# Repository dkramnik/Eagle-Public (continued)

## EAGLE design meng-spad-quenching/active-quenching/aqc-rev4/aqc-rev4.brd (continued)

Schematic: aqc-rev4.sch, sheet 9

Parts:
C26: CAP ALUM POLY 47UF 20% 20V SMD; CT7343
C79, C106, C107: CAP CER 0.1UF 25V X7R 0603 10%; C0603
C95: CAP CER 0.1UF 10V X7R 0402 10%; C0402
C97: CAP CER 10000PF 10V X7R 0402 10%; C0402
C98, C101: CAP CER 47PF 16V C0G 0402 5%; C0402
C105: CAP CER 10000PF 25V X7R 0603 10%; C0603
C108: CAP CER 4.7UF 6.3V X7R 0603 10%; C0603
H1, H2, H3, H4: MOUNT-PAD-ROUND3.2; 3,2-PAD
IC29: USBLC6-2SC6Y; SOT23-6L
IC32: LM1117; SOT-223
L8, L10: MI0805J102R-10; R0805
Q1: DMG2305UX-13; SOT23-WIDE
R58: RES SMD 4.7K OHM 1% 1/10W 0603; R0603
R62: RES SMD 100K OHM 1% 1/10W 0603; R0603
R67, R70: RES SMD 22 OHM 1% 1/10W 0402; R0402
TP23: TPTP15R; TP15R
X3, X6: KEYSTONE-7774
X8: 61729-0010BLF; PN61729-S

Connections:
!MCU_SMPS_PRECHG: R58.2; also elsewhere on the board
GND: C26.-, C95.2, C97.2, C98.2, C101.2, C105.2, C106.2, C107.2, C108.2, H1.B3,2, H2.B3,2, H3.B3,2, H4.B3,2, IC29.2 (GND), IC32.1 (GND), L10.2, X3.1, X3.2, X3.3, X3.4, X6.1, X6.2, X6.3, X6.4, X8.S1, X8.S2; also elsewhere on the board
MCU_USB_FS_D_N: C101.1, R70.1; also elsewhere on the board
MCU_USB_FS_D_P: C98.1, R67.1; also elsewhere on the board
unnamed: C79.1, Q1.1 (G), R58.1, R62.1
PP_P3V3: C95.1, C97.1, C106.1, IC29.5 (VBUS), IC32.2 (OUT), IC32.4 (TAB), TP23.TP; also elsewhere on the board
SMPS_USB_VDD: C26.+, C79.2, Q1.3 (D); also elsewhere on the board
USBCONN_P1: C105.1, L8.1, X8.1
USBCONN_P4: L10.1, X8.4
USBD_CONN_N: IC29.3 (I/O2), X8.2
USBD_CONN_P: IC29.1 (I/O1_1), X8.3
USBD_TVS_N: IC29.4 (I/O2_2), R70.2
USBD_TVS_P: IC29.6 (I/O1_2), R67.2
USB_VDD: C107.1, C108.1, IC32.3 (IN), L8.2, Q1.2 (S), R62.2

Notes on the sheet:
USB INPUT AND INRUSH LIMITING
3.0
1 of 1

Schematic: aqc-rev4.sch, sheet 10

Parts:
C3: CAP CER 1000PF 50V X7R 0603 10%; C0603
C4: CAP CER 1300PF 50V C0G 0603 5%; C0603
C13, C14, C25: CAP ALUM POLY 47UF 20% 20V SMD; CT7343
C15: CAP CER 4.7UF 25V X7R 0805 10%; C0805
C17: CAP CER 0.1UF 25V X7R 0603 10%; C0603
C18: CAP CER 0.015UF 50V X7R 0603 10%; C0603
C19: CAP CER 220PF 50V C0G 0603 5%; C0603
D1: CDBA140SL-HF; DO214AC
IC3: LT1534-1; SO16
L1: 25n; R0603
L2: Wurth-7447709471; WE_INDUCTOR_SIZE_CODE_1210
L3: SRF0703-820M; SRF0703
R3: RES SMD 0 OHM JUMPER 0603; R0603
R4, R9: DNP; R0603
R5: RES SMD 29.4K OHM 1% 1/10W 0603; R0603
R6: RES SMD 2.49K OHM 1% 1/10W 0603; R0603
R7: RES SMD 10 OHM 1% 1/10W 0603; R0603
R8: RES SMD 16.9K OHM 1% 1/10W 0603; R0603
R14, R15: RES SMD 1K OHM 1% 1/10W 0603; R0603
R16: RES SMD 6.8K OHM 1% 1/10W 0603; R0603
TP2, TP7: TPB1,27; B1,27

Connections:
!MCU_SHDN_BOOST: IC3.12 (!SHDN); also elsewhere on the board
BOOST_STAGE1: C13.+, C14.+, D1.C, L3.1, R4.1, R9.1
BOOST_SW_NODE: D1.A, IC3.2 (COL), L2.2, R7.1
GND: C3.1, C4.2, C13.-, C14.-, C15.2, C17.2, C18.2, C19.2, C25.-, IC3.1 (GND), IC3.8 (GND), IC3.9 (GND), IC3.16 (GND), L1.2, R6.2, R8.1, R14.2, R15.2; also elsewhere on the board
LBOOST_2: L3.2, L3.3
unnamed: IC3.7 (FB), R5.1, R6.1
unnamed: IC3.3 (PGND), L1.1
unnamed: C4.1, IC3.5 (CT)
unnamed: IC3.13 (RCSL), R15.1
unnamed: IC3.14 (RVSL), R14.1
unnamed: C3.2, R7.2
unnamed: C18.1, R16.1
unnamed: C19.1, IC3.11 (VC), R16.2
unnamed: IC3.6 (RT), R8.2
unnamed: R3.2, R4.2, R5.2
PP_P16V0_BOOST: C25.+, L3.4, R3.1, R9.2; also elsewhere on the board
SMPS_USB_VDD: C15.1, C17.1, IC3.15 (VIN), L2.1; also elsewhere on the board
TP_NFB_BOOST: IC3.10 (NFB), TP7.TP
TP_SYNC_BOOST: IC3.4 (SYNC), TP2.TP

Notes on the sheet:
POSITIVE DC/DC SMPS
3.0
1 of 1

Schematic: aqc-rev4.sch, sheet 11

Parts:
C27: CAP CER 10UF 10V X7R 1206 10%; C1206
C31: CAP CER 10000PF 25V X7R 0603 10%; C0603
C32: CAP CER 1300PF 50V C0G 0603 5%; C0603
C42: CAP ALUM POLY 68UF 20% 16V SMD; CT7343
C45, C57: CAP CER 4.7UF 25V X7R 0805 10%; C0805
C56: CAP CER 10UF 16V X7R 0805 20%; C0805
C67: CAP CER 0.1UF 25V X7R 0603 10%; C0603
C68: CAP CER 0.033UF 50V X7R 0603 10%; C0603
C69, C71: DNP; C0603
D2: CDBA140SL-HF; DO214AC
IC10: LT1534-1; SO16
L5: 25n; R0603
L6: SRF0703-820M; SRF0703
R29: RES SMD 100 OHM 1% 1/8W 0603; R0603
R30: RES SMD 16.9K OHM 1% 1/10W 0603; R0603
R41: RES SMD 1.4K OHM 1% 1/10W 0603; R0603
R43, R44, R48: RES SMD 1K OHM 1% 1/10W 0603; R0603
R45: RES SMD 2K OHM 1% 1/10W 0603; R0603
TP8, TP10: TPB1,27; B1,27

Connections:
!MCU_SHDN_CUK: IC10.12 (!SHDN); also elsewhere on the board
GND: C27.2, C31.2, C32.2, C45.2, C56.2, C57.2, C67.2, C68.2, C69.2, C71.2, D2.C, IC10.1 (GND), IC10.8 (GND), IC10.9 (GND), IC10.16 (GND), L5.2, R30.1, R43.2, R44.2, R48.2; also elsewhere on the board
unnamed: C32.1, IC10.5 (CT)
unnamed: IC10.3 (PGND), L5.1
unnamed: IC10.13 (RCSL), R44.1
unnamed: IC10.14 (RVSL), R43.1
unnamed: C31.1, R29.2
unnamed: C68.1, R45.1
unnamed: C69.1, IC10.11 (VC), R45.2
unnamed: IC10.6 (RT), R30.2
unnamed: IC10.10 (NFB), R41.2, R48.1
unnamed: C42.+, IC10.2 (COL), L6.3, R29.1
unnamed: C42.-, C71.1, D2.A, L6.4
PP_N6V0_CUK: C56.1, L6.2, R41.1; also elsewhere on the board
SMPS_USB_VDD: C27.1, C45.1, C57.1, C67.1, IC10.15 (VIN), L6.1; also elsewhere on the board
TP_FB_CUK: IC10.7 (FB), TP10.TP
TP_SYNC_CUK: IC10.4 (SYNC), TP8.TP

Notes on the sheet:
NEGATIVE DC/DC SMPS
3.0
1 of 1

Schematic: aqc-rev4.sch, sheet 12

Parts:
C1, C2, C5, C6, C41, C54: CAP CER 10000PF 25V X7R 0603 10%; C0603
C7, C8, C9, C10, C46, C53: CAP CER 0.1UF 25V X7R 0603 10%; C0603
C11: CAP CER 10UF 25V X5R 0805 10%; C0805
C12, C39: CAP CER 10UF 16V X7R 0805 20%; C0805
IC1, IC2: TPS7A4901; MSOP-8_POWER_PAD
IC9: TPS7A3001; MSOP-8_POWER_PAD
R1, R34: RES SMD 24K OHM 1% 1/10W 0603; R0603
R2: RES SMD 11.8K OHM 1% 1/10W 0603; R0603
R10, R32: RES SMD 76.8K OHM 1% 1/10W 0603; R0603
R11: RES SMD 137K OHM 1% 1/10W 0603; R0603
TP1, TP3, TP4, TP11: TPTP15R; TP15R

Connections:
GND: C1.2, C2.2, C7.2, C8.2, C9.2, C10.2, C11.2, C12.2, C39.2, C46.2, C53.2, C54.2, IC1.4 (GND), IC1.PAD (GND), IC2.4 (GND), IC2.PAD (GND), IC9.4 (GND), IC9.PAD (GND), R1.2, R2.2, R34.2, TP4.TP; also elsewhere on the board
LDO_N10V0_FB_CH1: C41.2, IC9.2 (FB), R32.1, R34.1
LDO_N10V0_NR_SS_CH1: C54.1, IC9.6 (NR/SS)
LDO_P5V0_FB_CH1: C5.2, IC1.2 (FB), R1.1, R10.1
LDO_P5V0_NR_SS_CH1: C1.1, IC1.6 (NR/SS)
LDO_P10V0_FB_CH1: C6.2, IC2.2 (FB), R2.1, R11.1
LDO_P10V0_NR_SS_CH1: C2.1, IC2.6 (NR/SS)
PP_N5V0_ANALOG: C39.1, C41.1, C46.1, IC9.1 (OUT), R32.2, TP11.TP; also elsewhere on the board
PP_N6V0_CUK: C53.1, IC9.5 (EN), IC9.8 (IN); also elsewhere on the board
PP_P5V0_ANALOG: C5.1, C9.1, C12.1, IC1.1 (OUT), R10.2, TP3.TP; also elsewhere on the board
PP_P15V0_ANALOG: C6.1, C7.1, C10.1, C11.1, IC1.5 (EN), IC1.8 (IN), IC2.1 (OUT), R11.2, TP1.TP; also elsewhere on the board
PP_P16V0_BOOST: C8.1, IC2.5 (EN), IC2.8 (IN); also elsewhere on the board

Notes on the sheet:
LINEAR POSTREGULATORS
3.0
1 of 1

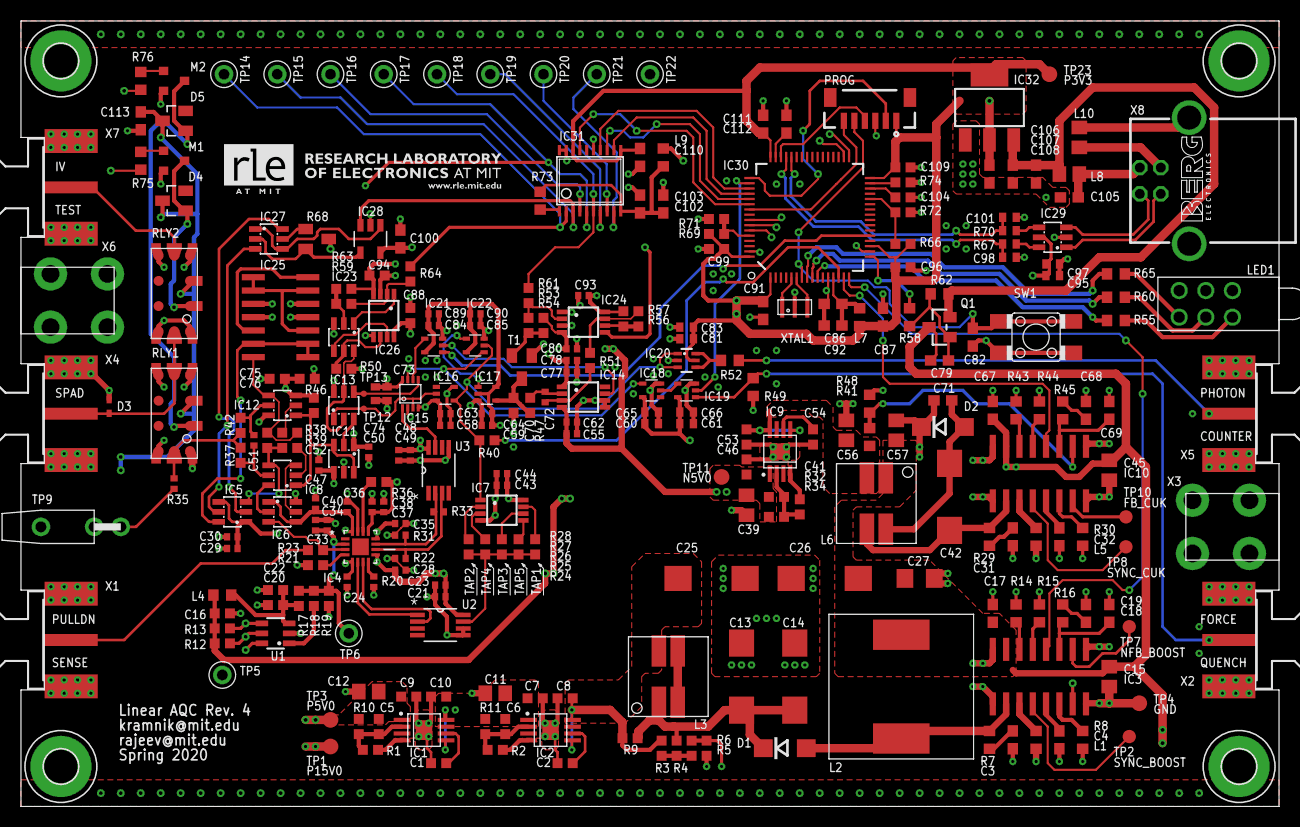
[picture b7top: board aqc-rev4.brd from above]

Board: 4 copper layers, 120.0 x 74.9 mm, 285 parts (0 on the bottom side), 166 nets.

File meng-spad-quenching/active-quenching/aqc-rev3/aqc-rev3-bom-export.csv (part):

"Qty";"Value";"Device";"Package";"Parts";"Description";"MF";"MPN";"OC_FARNELL";"OC_NEWARK";"PACKAGE";"PROD_ID";"SUPPLIER";"TP_SIGNAL_NAME";"VALUE";
"6";"0R";"R-EU_R0603";"R0603";"R3, R47, R51, R71, R73, R74";"RESISTOR, European symbol";"";"";"";"";"";"";"";"";"";
"1";"100R";"R-EU_R0402";"R0402";"R33";"RESISTOR, European symbol";"";"";"";"";"";"";"";"";"";
"3";"100R";"R-EU_R0603";"R0603";"R29, R75, R76";"RESISTOR, European symbol";"";"";"";"";"";"";"";"";"";
"2";"100R, 1%";"R-EU_R0603";"R0603";"R37, R42";"RESISTOR, European symbol";"";"";"";"";"";"";"";"";"";
"3";"100k";"R-EU_R0603";"R0603";"R56, R57, R62";"RESISTOR, European symbol";"";"";"";"";"";"";"";"";"";
"21";"100n";"C-EUC0402";"C0402";"C23, C29, C33, C35, C36, C37, C43, C49, C55, C58, C59, C61, C65, C73, C77, C80, C83, C89, C90, C93, C95";"CAPACITOR, European symbol";"";"";"";"";"";"";"";"";"";
"28";"100n";"C-EUC0603";"C0603";"C7, C8, C9, C10, C16, C17, C20, C46, C53, C67, C76, C79, C88, C91, C92, C94, C96, C99, C100, C102, C104, C106, C107, C109, C110, C111, C112, C113";"CAPACITOR, European symbol";"";"";"";"";"";"";"";"";"";
"1";"100p";"C-EUC0402";"C0402";"C51";"CAPACITOR, European symbol";"";"";"";"";"";"";"";"";"";
"1";"100p";"C-EUC0603";"C0603";"C70";"CAPACITOR, European symbol";"";"";"";"";"";"";"";"";"";
"1";"102k, 1%";"R-EU_R0603";"R0603";"R64";"RESISTOR, European symbol";"";"";"";"";"";"";"";"";"";
"1";"10R";"R-EU_R0603";"R0603";"R7";"RESISTOR, European symbol";"";"";"";"";"";"";"";"";"";
"2";"10k";"R-EU_R0603";"R0603";"R36, R54";"RESISTOR, European symbol";"";"";"";"";"";"";"";"";"";
"22";"10n";"C-EUC0402";"C0402";"C21, C24, C28, C30, C34, C38, C40, C44, C47, C48, C50, C60, C62, C63, C64, C66, C74, C78, C81, C84, C85, C97";"CAPACITOR, European symbol";"";"";"";"";"";"";"";"";"";
"11";"10n";"C-EUC0603";"C0603";"C1, C2, C5, C6, C31, C41, C52, C54, C75, C82, C105";"CAPACITOR, European symbol";"";"";"";"";"";"";"";"";"";
"3";"10u";"C-EUC0805";"C0805";"C11, C12, C39";"CAPACITOR, European symbol";"";"";"";"";"";"";"";"";"";
"1";"10u";"C-EUC1206";"C1206";"C27";"CAPACITOR, European symbol";"";"";"";"";"";"";"";"";"";
"1";"10u, 10V";"C-EUC0805";"C0805";"C56";"CAPACITOR, European symbol";"";"";"";"";"";"";"";"";"";
"1";"110R, 1%";"R-EU_R0603";"R0603";"R50";"RESISTOR, European symbol";"";"";"";"";"";"";"";"";"";
"1";"11k8";"R-EU_R0603";"R0603";"R2";"RESISTOR, European symbol";"";"";"";"";"";"";"";"";"";
"1";"127k, 1%";"R-EU_R0603";"R0603";"R59";"RESISTOR, European symbol";"";"";"";"";"";"";"";"";"";
"2";"1300p";"C-EUC0603";"C0603";"C4, C32";"CAPACITOR, European symbol";"";"";"";"";"";"";"";"";"";
"1";"137k";"R-EU_R0603";"R0603";"R11";"RESISTOR, European symbol";"";"";"";"";"";"";"";"";"";
"2";"150R";"R-EU_R0402";"R0402";"R22, R31";"RESISTOR, European symbol";"";"";"";"";"";"";"";"";"";
"1";"15n";"C-EUC0603";"C0603";"C18";"CAPACITOR, European symbol";"";"";"";"";"";"";"";"";"";
"2";"16k9";"R-EU_R0603";"R0603";"R8, R30";"RESISTOR, European symbol";"";"";"";"";"";"";"";"";"";
"6";"1k";"R-EU_R0603";"R0603";"R14, R15, R18, R43, R44, R48";"RESISTOR, European symbol";"";"";"";"";"";"";"";"";"";
"1";"1k4";"R-EU_R0603";"R0603";"R41";"RESISTOR, European symbol";"";"";"";"";"";"";"";"";"";
"1";"1n";"C-EUC0603";"C0603";"C3";"CAPACITOR, European symbol";"";"";"";"";"";"";"";"";"";
"2";"200R, 1%";"R-EU_R0603";"R0603";"R38, R39";"RESISTOR, European symbol";"";"";"";"";"";"";"";"";"";
"2";"220R, 1%";"R-EU_R0603";"R0603";"R23, R46";"RESISTOR, European symbol";"";"";"";"";"";"";"";"";"";
"2";"220k";"R-EU_R0603";"R0603";"R53, R61";"RESISTOR, European symbol";"";"";"";"";"";"";"";"";"";
"1";"220p";"C-EUC0603";"C0603";"C19";"CAPACITOR, European symbol";"";"";"";"";"";"";"";"";"";
"2";"22R";"R-EU_R0402";"R0402";"R67, R70";"RESISTOR, European symbol";"";"";"";"";"";"";"";"";"";
"2";"24k";"R-EU_R0603";"R0603";"R1, R34";"RESISTOR, European symbol";"";"";"";"";"";"";"";"";"";
"2";"25n";"INDUCTOR0603";"R0603";"L1, L5";"";"";"";"";"";"";"";"";"";"";
"1";"274R, 1%";"R-EU_R0603";"R0603";"R63";"RESISTOR, European symbol";"";"";"";"";"";"";"";"";"";
"1";"29k4";"R-EU_R0603";"R0603";"R5";"RESISTOR, European symbol";"";"";"";"";"";"";"";"";"";
"1";"2k";"R-EU_R0603";"R0603";"R45";"RESISTOR, European symbol";"";"";"";"";"";"";"";"";"";
"2";"2k2";"R-EU_R0603";"R0603";"R12, R13";"RESISTOR, European symbol";"";"";"";"";"";"";"";"";"";
"1";"2k49";"R-EU_R0603";"R0603";"R6";"RESISTOR, European symbol";"";"";"";"";"";"";"";"";"";
"1";"33n";"C-EUC0603";"C0603";"C68";"CAPACITOR, European symbol";"";"";"";"";"";"";"";"";"";
"3";"470R";"R-EU_R0603";"R0603";"R55, R60, R65";"RESISTOR, European symbol";"";"";"";"";"";"";"";"";"";
"2";"47p";"C-EUC0402";"C0402";"C98, C101";"CAPACITOR, European symbol";"";"";"";"";"";"";"";"";"";
"4";"47u, 20V";"CPOL-EUCT7343";"CT7343";"C13, C14, C25, C26";"POLARIZED CAPACITOR, European symbol";"";"";"";"";"";"";"";"";"";
"2";"49R9";"R-EU_R0402";"R0402";"R20, R35";"RESISTOR, European symbol";"";"";"";"";"";"";"";"";"";
"3";"49R9";"R-EU_R0603";"R0603";"R40, R49, R52";"RESISTOR, European symbol";"";"";"";"";"";"";"";"";"";
"1";"4k7";"R-EU_R0603";"R0603";"R58";"RESISTOR, European symbol";"";"";"";"";"";"";"";"";"";
"5";"4u7";"C-EUC0603";"C0603";"C22, C86, C87, C103, C108";"CAPACITOR, European symbol";"";"";"";"";"";"";"";"";"";
"3";"4u7";"C-EUC0805";"C0805";"C15, C45, C57";"CAPACITOR, European symbol";"";"";"";"";"";"";"";"";"";
"1";"5640200132F";"CBI-564-0X00-XXX-3LED";"CBI-564-0X00-XXX";"LED1";"";"";"";"";"";"";"";"";"";"564-0x00-xxx";
"1";"68u, 16V";"CPOL-EUCT7343";"CT7343";"C42";"POLARIZED CAPACITOR, European symbol";"";"";"";"";"";"";"";"";"";
"1";"6k8";"R-EU_R0603";"R0603";"R16";"RESISTOR, European symbol";"";"";"";"";"";"";"";"";"";
"1";"732-1699-2-ND";"WE_INDUCTOR";"WE_INDUCTOR_SIZE_CODE_1210";"L2";"";"";"";"";"";"";"";"";"";"";
"1";"74AHC1G04DCK";"74AHC1G04DCK";"SC70-5";"IC18";"INVERTER Gate";"";"";"";"";"";"";"";"";"";
"2";"74AHC1G08DCK";"74AHC1G08DCK";"SC70-5";"IC21, IC22";"2-input AND gate";"";"";"";"";"";"";"";"";"";
"1";"74AHC1G14DCK";"74AHC1G14DCK";"SC70-5";"IC16";"Single Schmitt-Trigger Inverter Gate";"";"";"";"";"";"";"";"";"";
"1";"74AHC1G32DCK";"74AHC1G32DCK";"SC70-5";"IC19";"2-input OR gate";"";"";"";"";"";"";"";"";"";
"2";"76k8";"R-EU_R0603";"R0603";"R10, R32";"RESISTOR, European symbol";"";"";"";"";"";"";"";"";"";
"1";"ADCMP582";"ADCMP582";"QFN50P300X300X80-16N";"IC4";"Ultrafast SiGe Voltage Comparator w/. PECL Outputs";"";"";"";"";"";"";"";"";"";
"2";"BAS40";"BAS40";"SOT23";"D4, D5";"Silicon Schottky Diodes";"";"";"";"";"";"";"";"";"";
"2";"BSS806N";"BSS806N";"SOT23R_INFINEON";"M1, M2";"";"";"";"";"";"";"";"";"";"";
"2";"CDBA140SL-HF";"DIODE-DO214AC";"DO214AC";"D1, D2";"DIODE";"";"";"";"";"";"";"";"";"";
"1";"CONN_FORCE_QUENCH";"SMA-142-0701-881/886";"J502-ND-142-0701-881/886";"X2";"SMA 50 Ohm End Launch Jack Receptacle - Round Contact";"JOHNSON COMPONENTS";"142-0711-871";"unknown";"01C1639";"";"";"";"";"";
"1";"CONN_PHOTON_COUNTER";"SMA-142-0701-881/886";"J502-ND-142-0701-881/886";"X5";"SMA 50 Ohm End Launch Jack Receptacle - Round Contact";"JOHNSON COMPONENTS";"142-0701-881";"1608603";"08B906";"";"";"";"";"";
"1";"CONN_PULLDN_SENSE";"SMA-142-0701-881/886";"J502-ND-142-0701-881/886";"X1";"SMA 50 Ohm End Launch Jack Receptacle - Round Contact";"JOHNSON COMPONENTS";"142-0711-871";"unknown";"01C1639";"";"";"";"";"";
"1";"CONN_SMU";"SMA-142-0701-881/886";"J502-ND-142-0701-881/886";"X7";"SMA 50 Ohm End Launch Jack Receptacle - Round Contact";"JOHNSON COMPONENTS";"142-0701-881";"1608603";"08B906";"";"";"";"";"";
"1";"CONN_SPAD";"SMA-142-0701-881/886";"J502-ND-142-0701-881/886";"X4";"SMA 50 Ohm End Launch Jack Receptacle - Round Contact";"JOHNSON COMPONENTS";"142-0701-881";"1608603";"08B906";"";"";"";"";"";
"2";"CRF05-1A";"MEDER_CRF05-1A";"MEDER_RELAY_CRF";"RLY1, RLY2";"MEDER CRF05-1A RF Reed Relay in a ceramic surface mount package.";"";"";"";"";"";"";"";"";"CRF05-1A";
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
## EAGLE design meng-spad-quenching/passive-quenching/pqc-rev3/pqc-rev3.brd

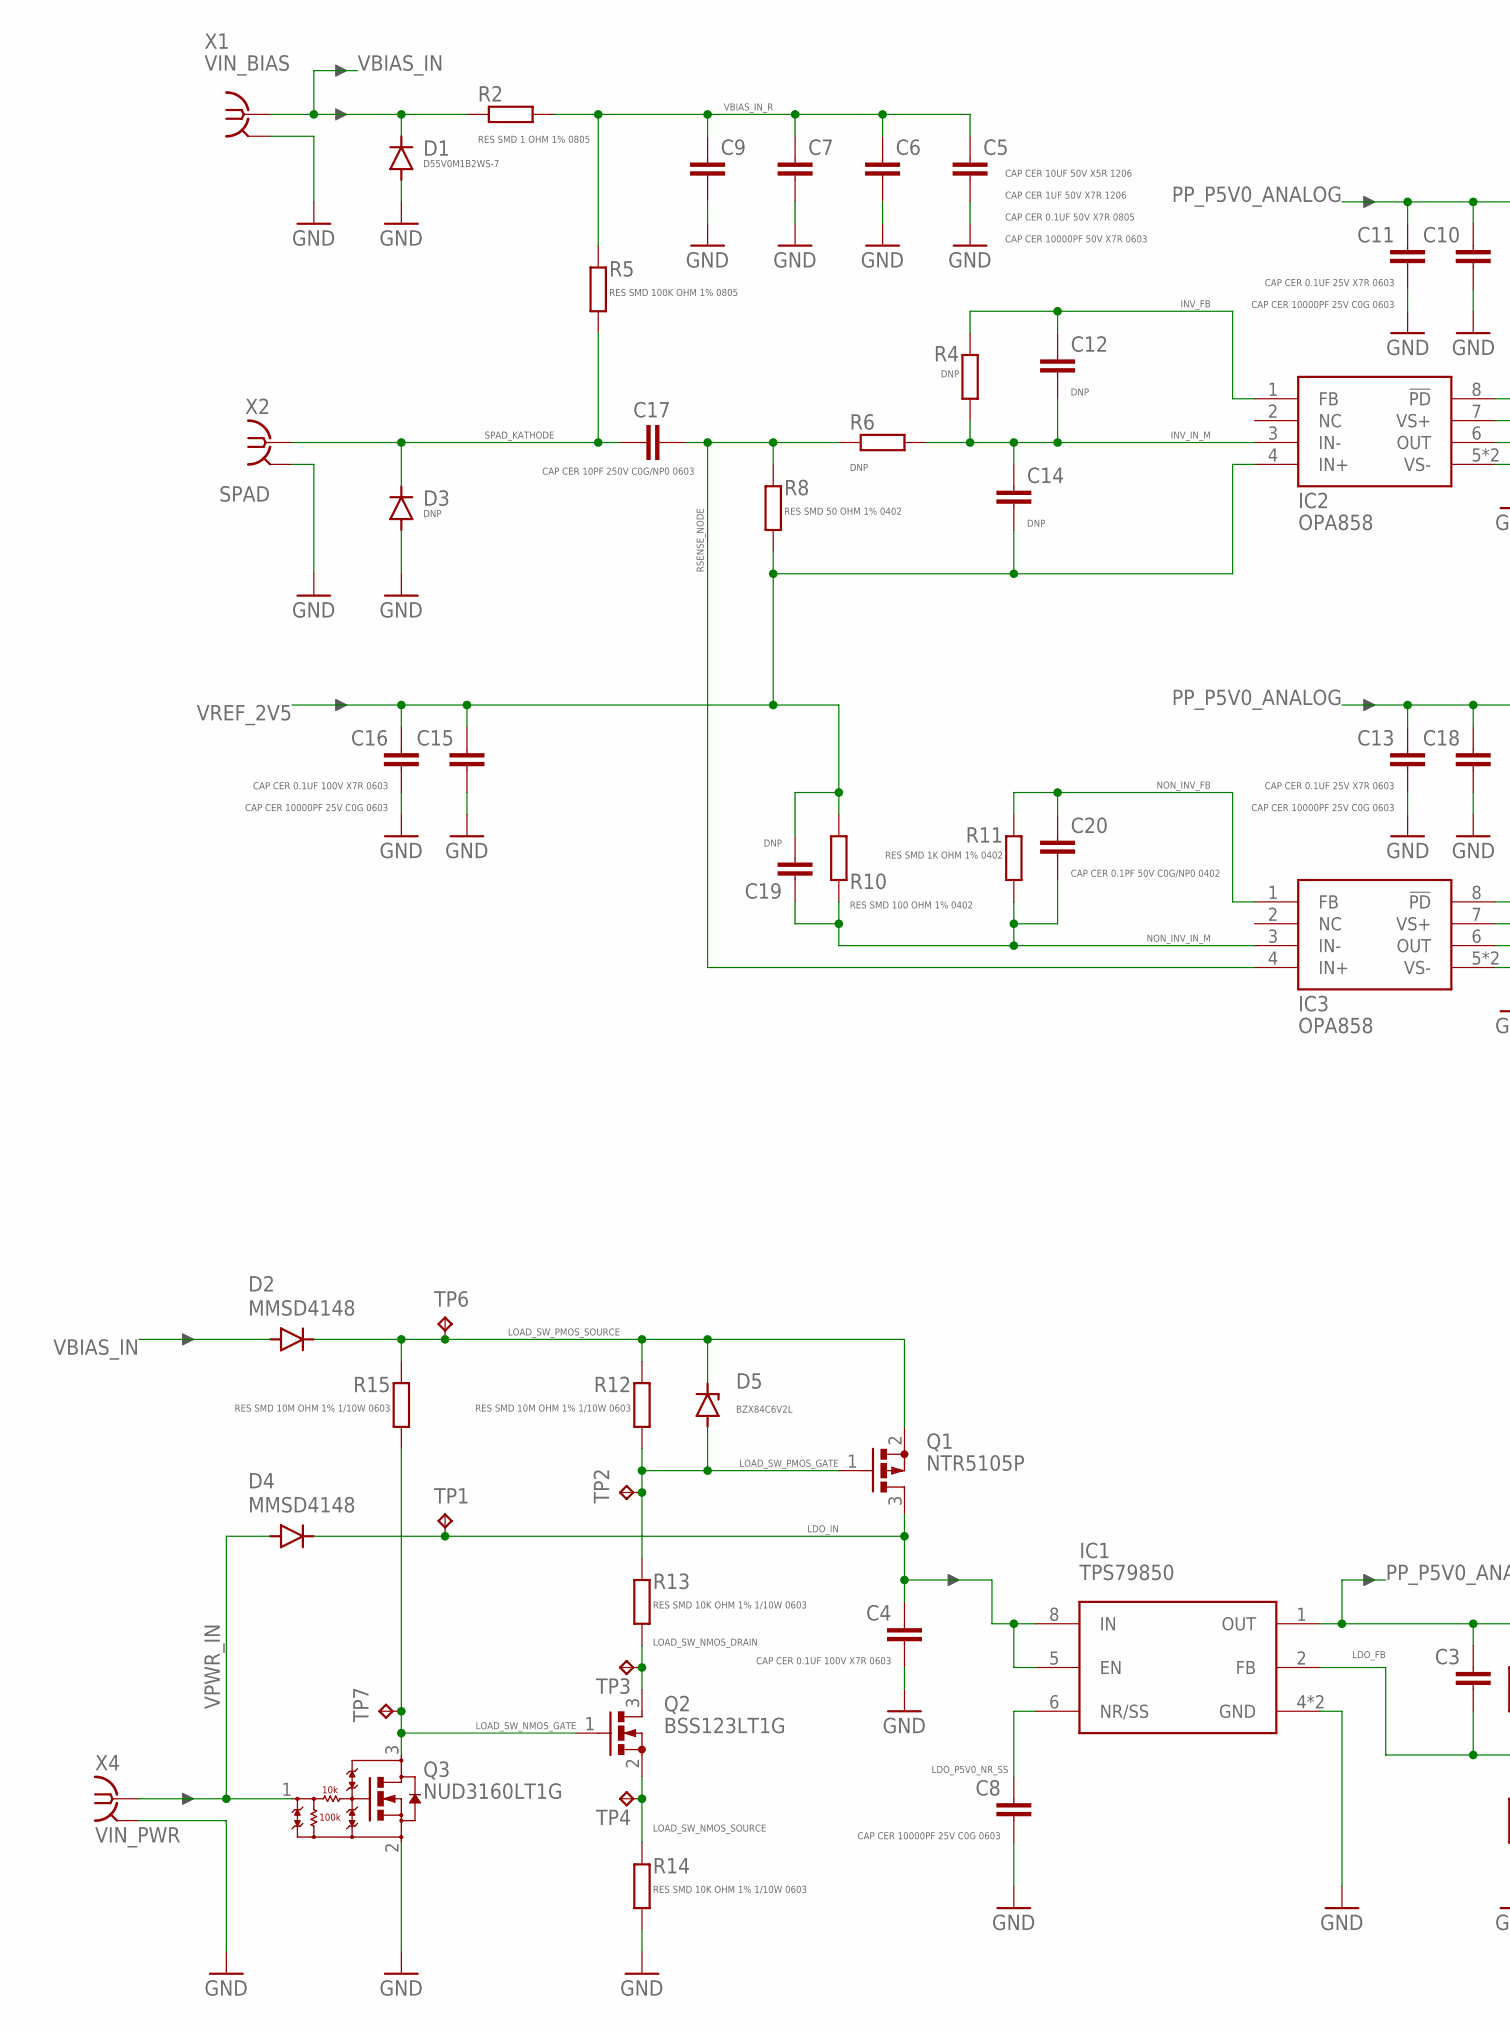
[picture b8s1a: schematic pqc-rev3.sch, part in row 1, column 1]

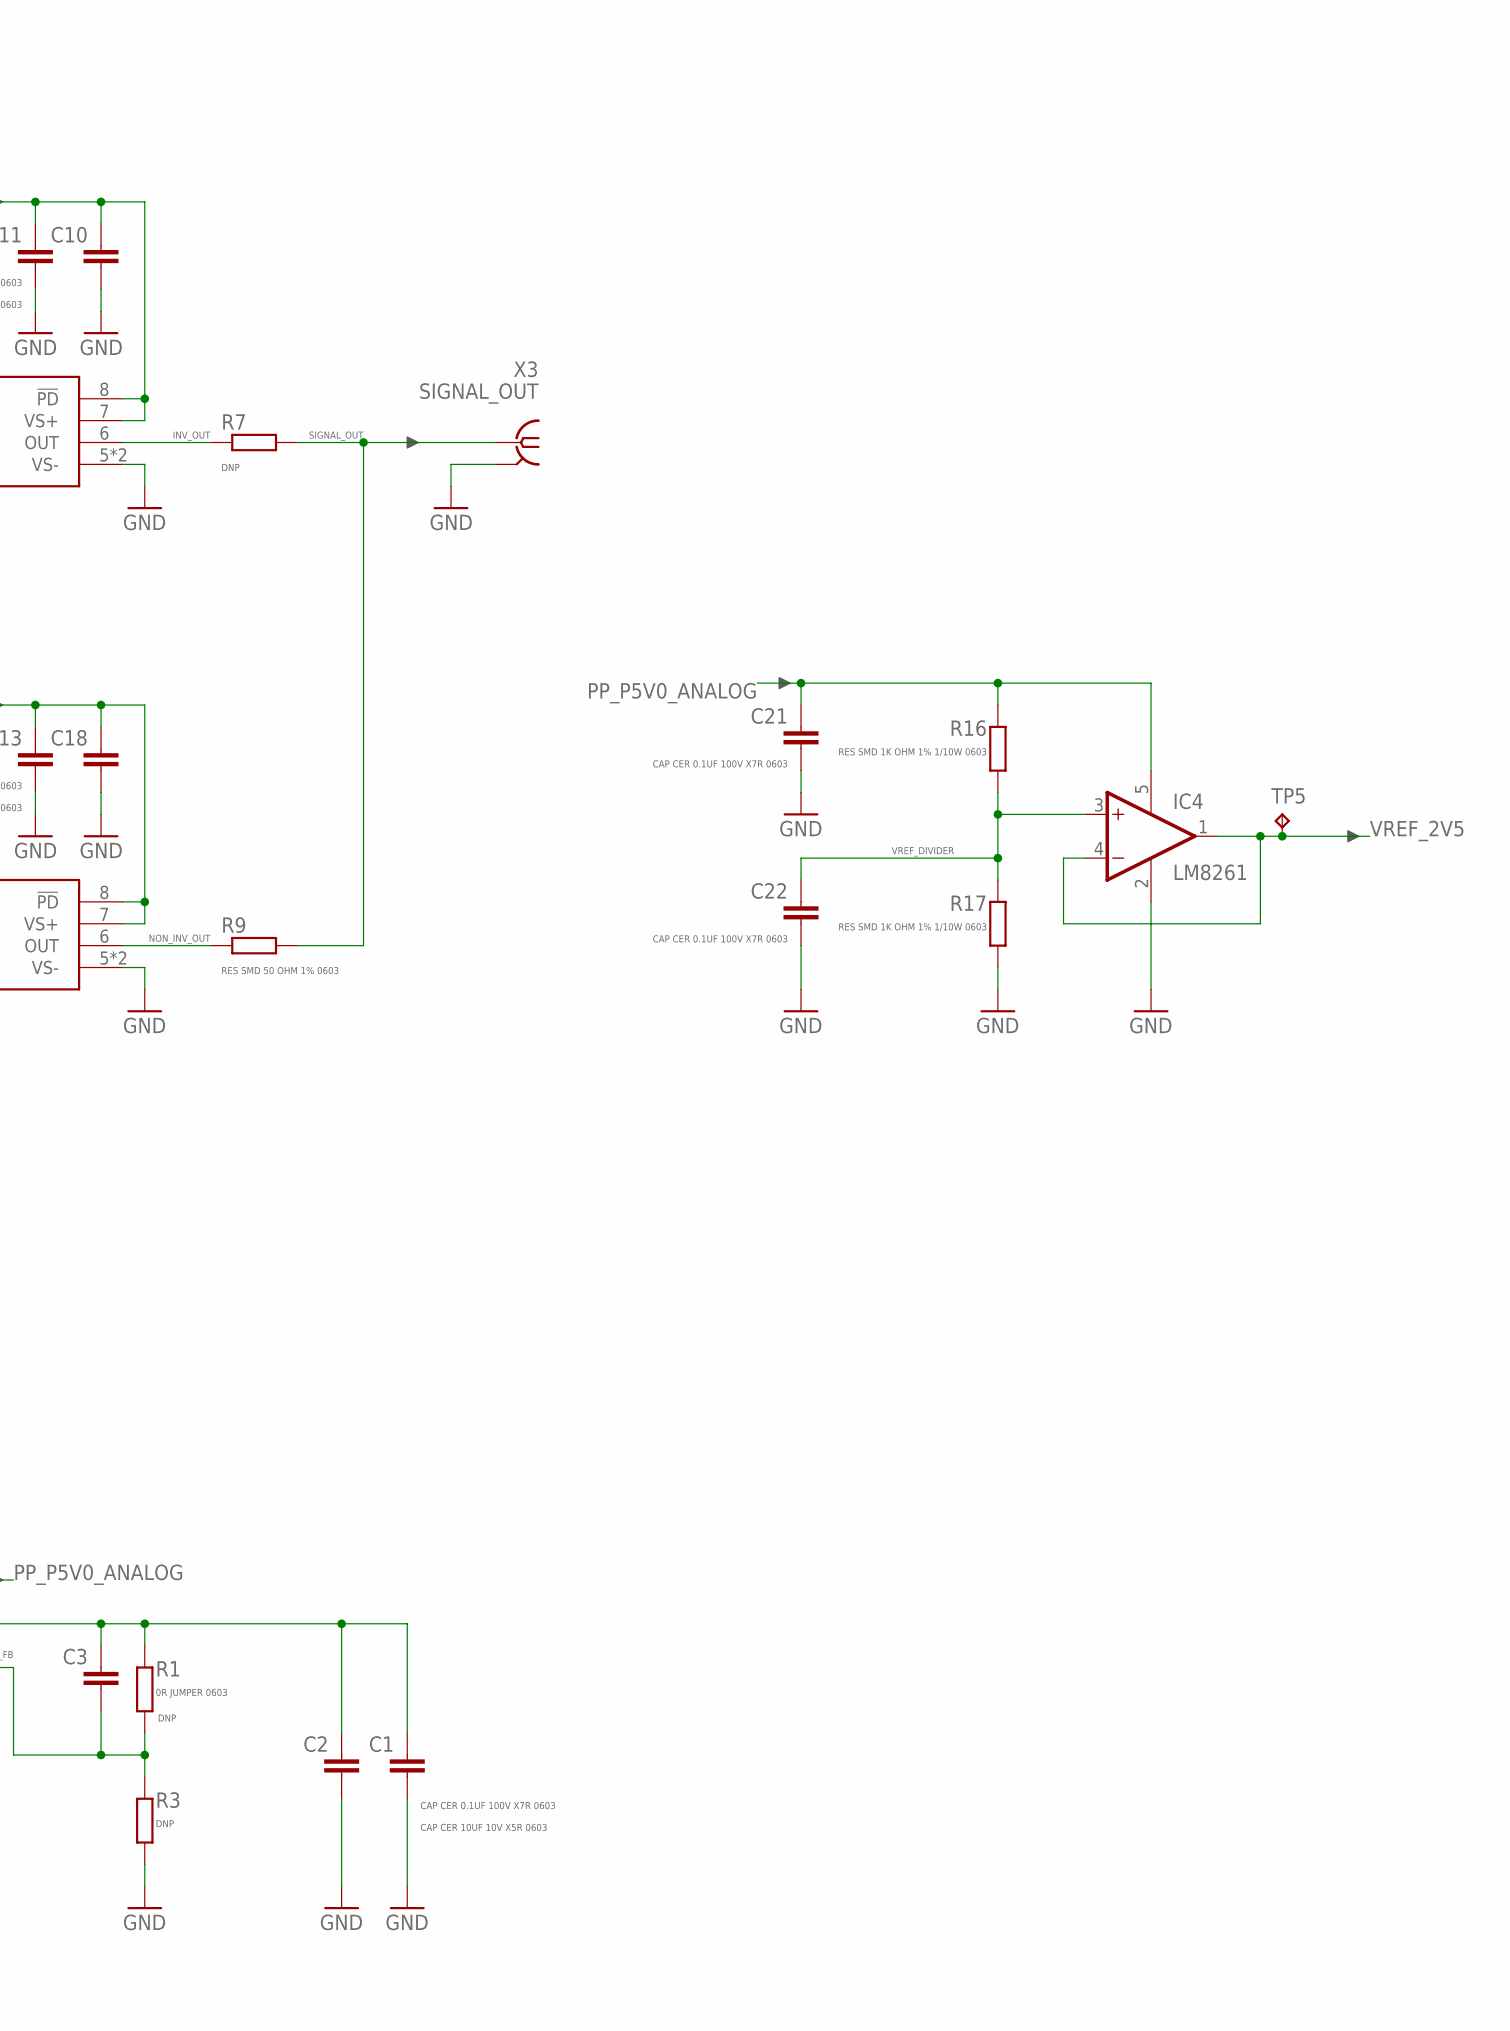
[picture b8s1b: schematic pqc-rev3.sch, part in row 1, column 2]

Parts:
C1: CAP CER 10UF 10V X5R 0603; C0603
C2, C4, C16, C21, C22: CAP CER 0.1UF 100V X7R 0603; C0603
C3: DNP; C0603
C5: CAP CER 10UF 50V X5R 1206; C1206
C6: CAP CER 1UF 50V X7R 1206; C1206
C7: CAP CER 0.1UF 50V X7R 0805; C0805
C8, C10, C15, C18: CAP CER 10000PF 25V C0G 0603; C0603
C9: CAP CER 10000PF 50V X7R 0603; C0603
C11, C13: CAP CER 0.1UF 25V X7R 0603; C0603
C12, C14, C19: DNP; C0402
C17: CAP CER 10PF 250V C0G/NP0 0603; C0603
C20: CAP CER 0.1PF 50V C0G/NP0 0402; C0402
D1: D55V0M1B2WS-7; SOD323-W
D2, D4: MMSD4148; SOD123
D3: DNP; SOD323-W
D5: BZX84C6V2L; SOT23
IC1: TPS79850; MSOP-8_POWER_PAD
IC2, IC3: OPA858; WSON8
IC4: LM8261; SOT23-5
Q1: NTR5105P; SOT23C
Q2: BSS123LT1G; SOT23C
Q3: NUD3160LT1G; SOT23C
R1: 0R JUMPER 0603; R0603
R2: RES SMD 1 OHM 1% 0805; R0805
R3, R7: DNP; R0603
R4, R6: DNP; R0402
R5: RES SMD 100K OHM 1% 0805; R0805
R8: RES SMD 50 OHM 1% 0402; R0402
R9: RES SMD 50 OHM 1% 0603; R0603
R10: RES SMD 100 OHM 1% 0402; R0402
R11: RES SMD 1K OHM 1% 0402; R0402
R12, R15: RES SMD 10M OHM 1% 1/10W 0603; R0603
R13, R14: RES SMD 10K OHM 1% 1/10W 0603; R0603
R16, R17: RES SMD 1K OHM 1% 1/10W 0603; R0603
TP1, TP2, TP3, TP4, TP5, TP6: TPTP10R; TP10R
TP7: TPB1,27; B1,27
X1: VIN_BIAS; MMCX-J-P-X-ST-EM1-MKT
X2: SPAD; J502-ND-142-0701-881/886
X3: SIGNAL_OUT; MMCX-J-P-X-ST-EM1-MKT
X4: VIN_PWR; MMCX-J-P-X-ST-EM1-MKT

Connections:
GND: C1.2, C2.2, C4.2, C5.2, C6.2, C7.2, C8.2, C9.2, C10.2, C11.2, C13.2, C15.2, C16.2, C18.2, C21.2, C22.2, D1.A, D3.A, IC1.4 (GND), IC1.PAD (GND), IC2.5 (VS-), IC2.PAD (VS-), IC3.5 (VS-), IC3.PAD (VS-), IC4.2 (V-), Q3.2 (S), R3.2, R14.1, R17.1, X1.2@1 (GND), X1.2@2 (GND), X1.2@3 (GND), X1.2@4 (GND), X2.G@1 (GND), X2.G@2 (GND), X2.G@3 (GND), X2.G@4 (GND), X3.2@1 (GND), X3.2@2 (GND), X3.2@3 (GND), X3.2@4 (GND), X4.2@1 (GND), X4.2@2 (GND), X4.2@3 (GND), X4.2@4 (GND)
INV_FB: C12.1, IC2.1 (FB), R4.1
INV_IN_M: C12.2, C14.1, IC2.3 (IN-), R4.2, R6.1
INV_OUT: IC2.6 (OUT), R7.2
LDO_FB: C3.2, IC1.2 (FB), R1.1, R3.1
LDO_IN: C4.1, D4.C, IC1.5 (EN), IC1.8 (IN), Q1.3 (D), TP1.TP
LDO_P5V0_NR_SS: C8.1, IC1.6 (NR/SS)
LOAD_SW_NMOS_DRAIN: Q2.3 (D), R13.1, TP3.TP
LOAD_SW_NMOS_GATE: Q2.1 (G), Q3.3 (D), R15.1, TP7.TP
LOAD_SW_NMOS_SOURCE: Q2.2 (S), R14.2, TP4.TP
LOAD_SW_PMOS_GATE: D5.1 (A), Q1.1 (G), R12.1, R13.2, TP2.TP
LOAD_SW_PMOS_SOURCE: D2.C, D5.3 (C), Q1.2 (S), R12.2, R15.2, TP6.TP
NON_INV_FB: C20.1, IC3.1 (FB), R11.1
NON_INV_IN_M: C19.1, C20.2, IC3.3 (IN-), R10.1, R11.2
NON_INV_OUT: IC3.6 (OUT), R9.2
PP_P5V0_ANALOG: C1.1, C2.1, C3.1, C10.1, C11.1, C13.1, C18.1, C21.1, IC1.1 (OUT), IC2.7 (VS+), IC2.8 (!PD), IC3.7 (VS+), IC3.8 (!PD), IC4.5 (V+), R1.2, R16.2
RSENSE_NODE: C17.2, IC3.4 (IN+), R6.2, R8.2
SIGNAL_OUT: R7.1, R9.1, X3.1
SPAD_KATHODE: C17.1, D3.C, R5.1, X2.1
VBIAS_IN: D1.C, D2.A, R2.2, X1.1
VBIAS_IN_R: C5.1, C6.1, C7.1, C9.1, R2.1, R5.2
VPWR_IN: D4.A, Q3.1 (G), X4.1
VREF_2V5: C14.2, C15.1, C16.1, C19.2, IC2.4 (IN+), IC4.1 (OUT), IC4.4 (-IN), R8.1, R10.2, TP5.TP
VREF_DIVIDER: C22.1, IC4.3 (+IN), R16.1, R17.2

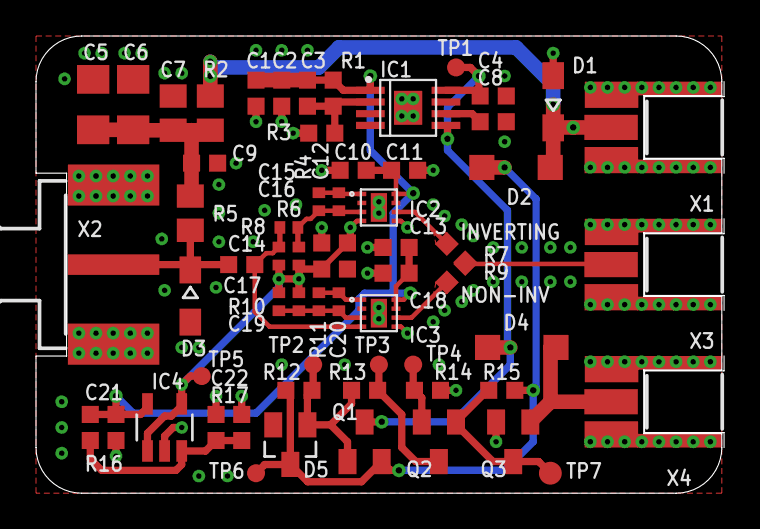
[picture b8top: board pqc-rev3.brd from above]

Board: 4 copper layers, 38.1 x 25.4 mm, 62 parts (0 on the bottom side), 24 nets.

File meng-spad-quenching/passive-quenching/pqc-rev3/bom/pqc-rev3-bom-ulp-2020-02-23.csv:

"Qty";"Value";"Device";"Package";"Parts";"Description";"MF";"MPN";"OC_FARNELL";"OC_NEWARK";"SPICEPREFIX";"TP_SIGNAL_NAME";"VALUE";
"1";"0R JUMPER 0603";"R-EU_R0603";"R0603";"R1";"RESISTOR, European symbol";"";"";"";"";"";"";"";
"1";"BSS123LT1G";"NMOS_GENERIC";"SOT23C";"Q2";"";"";"";"";"";"";"";"";
"1";"BZX84C6V2L";"ZENER-DIODESOT23";"SOT23";"D5";"Z-Diode";"";"";"";"";"";"";"";
"1";"CAP CER 0.1PF 50V C0G/NP0 0402";"C-EUC0402";"C0402";"C20";"CAPACITOR, European symbol";"";"";"";"";"";"";"";
"5";"CAP CER 0.1UF 100V X7R 0603";"C-EUC0603";"C0603";"C2, C4, C16, C21, C22";"CAPACITOR, European symbol";"";"";"";"";"";"";"";
"2";"CAP CER 0.1UF 25V X7R 0603";"C-EUC0603";"C0603";"C11, C13";"CAPACITOR, European symbol";"";"";"";"";"";"";"";
"1";"CAP CER 0.1UF 50V X7R 0805";"C-EUC0805";"C0805";"C7";"CAPACITOR, European symbol";"";"";"";"";"";"";"";
"3";"CAP CER 10000PF 25V C0G 0603";"C-EUC0603";"C0603";"C10, C15, C18";"CAPACITOR, European symbol";"";"";"";"";"";"";"";
"1";"CAP CER 10000PF 25V X7R 0603 10%";"C-EUC0603";"C0603";"C8";"CAPACITOR, European symbol";"";"";"";"";"";"";"";
"1";"CAP CER 10NF 50V X7R 0603";"C-EUC0603";"C0603";"C9";"CAPACITOR, European symbol";"";"";"";"";"";"";"";
"1";"CAP CER 10PF 250V C0G/NP0 0603";"C-EUC0603";"C0603";"C17";"CAPACITOR, European symbol";"";"";"";"";"";"";"";
"1";"CAP CER 10UF 10V X5R 0603";"C-EUC0603";"C0603";"C1";"CAPACITOR, European symbol";"";"";"";"";"";"";"";
"1";"CAP CER 10UF 50V X5R 1206";"C-EUC1206";"C1206";"C5";"CAPACITOR, European symbol";"";"";"";"";"";"";"";
"1";"CAP CER 1UF 50V X7R 1206";"C-EUC1206";"C1206";"C6";"CAPACITOR, European symbol";"";"";"";"";"";"";"";
"1";"D55V0M1B2WS-7";"DIODE-SOD323-W";"SOD323-W";"D1";"DIODE";"";"";"";"";"";"";"";
"3";"DNP";"C-EUC0402";"C0402";"C12, C14, C19";"CAPACITOR, European symbol";"";"";"";"";"";"";"";
"1";"DNP";"C-EUC0603";"C0603";"C3";"CAPACITOR, European symbol";"";"";"";"";"";"";"";
"1";"DNP";"DIODE-SOD323-W";"SOD323-W";"D3";"DIODE";"";"";"";"";"";"";"";
"1";"DNP";"OPA858";"WSON8";"IC2";"";"";"";"";"";"";"";"OPA858";
"2";"DNP";"R-EU_R0402";"R0402";"R4, R6";"RESISTOR, European symbol";"";"";"";"";"";"";"";
"2";"DNP";"R-EU_R0603";"R0603";"R3, R7";"RESISTOR, European symbol";"";"";"";"";"";"";"";
"1";"LM8261";"LM8261";"SOT23-5";"IC4";"";"";"";"";"";"";"";"LM8261";
"2";"MMSD4148";"DIODE-SOD123";"SOD123";"D2, D4";"DIODE";"";"";"";"";"";"";"";
"1";"NTR5105P";"PMOS_GENERIC_SOT23-3";"SOT23C";"Q1";"";"";"";"";"";"";"";"";
"1";"NUD3160LT1G";"NUD3160LT1G";"SOT23C";"Q3";"";"";"";"";"";"";"";"NUD3160LT1G";
"1";"OPA858";"OPA858";"WSON8";"IC3";"";"";"";"";"";"";"";"OPA858";
"1";"RES SMD 1 OHM 1% 0805";"R-EU_R0805";"R0805";"R2";"RESISTOR, European symbol";"";"";"";"";"R";"";"";
"1";"RES SMD 100 OHM 1% 0402";"R-EU_R0402";"R0402";"R10";"RESISTOR, European symbol";"";"";"";"";"";"";"";
"1";"RES SMD 100K OHM 1% 0805";"R-EU_R0805";"R0805";"R5";"RESISTOR, European symbol";"";"";"";"";"R";"";"";
"2";"RES SMD 10K OHM 1% 1/10W 0603";"R-EU_R0603";"R0603";"R13, R14";"RESISTOR, European symbol";"";"";"";"";"";"";"";
"2";"RES SMD 10M OHM 1% 1/10W 0603";"R-EU_R0603";"R0603";"R12, R15";"RESISTOR, European symbol";"";"";"";"";"";"";"";
"1";"RES SMD 1K OHM 1% 0402";"R-EU_R0402";"R0402";"R11";"RESISTOR, European symbol";"";"";"";"";"";"";"";
"2";"RES SMD 1K OHM 1% 1/10W 0603";"R-EU_R0603";"R0603";"R16, R17";"RESISTOR, European symbol";"";"";"";"";"";"";"";
"1";"RES SMD 50 OHM 1% 0402";"R-EU_R0402";"R0402";"R8";"RESISTOR, European symbol";"";"";"";"";"";"";"";
"1";"RES SMD 50 OHM 1% 0603";"R-EU_R0603";"R0603";"R9";"RESISTOR, European symbol";"";"";"";"";"";"";"";
"1";"SIGNAL_OUT";"COAX";"MMCX-J-P-X-ST-EM1-MKT";"X3";"MMCX STRAIGHT, EDGE MOUNT JACK- 50 OHM";"Samtec Inc.";"MMCX-J-P-X-ST-EM1-MKT";"unknown";"unknown";"";"";"";
"1";"SPAD";"SMA-142-0701-881/886";"J502-ND-142-0701-881/886";"X2";"SMA 50 Ohm End Launch Jack Receptacle - Round Contact";"JOHNSON COMPONENTS";"142-0701-881";"1608603";"08B906";"";"";"";
"1";"TPB1,27";"TPB1,27";"B1,27";"TP7";"Test pad";"";"";"";"";"";"";"";
"1";"TPS79850";"TPS7A";"MSOP-8_POWER_PAD";"IC1";"";"";"";"";"";"";"";"";
"6";"TPTP10R";"TPTP10R";"TP10R";"TP1, TP2, TP3, TP4, TP5, TP6";"Test pad";"";"";"";"";"";"";"";
"1";"VIN_BIAS";"COAX";"MMCX-J-P-X-ST-EM1-MKT";"X1";"MMCX STRAIGHT, EDGE MOUNT JACK- 50 OHM";"Samtec Inc.";"MMCX-J-P-X-ST-EM1-MKT";"unknown";"unknown";"";"";"";
"1";"VIN_PWR";"COAX";"MMCX-J-P-X-ST-EM1-MKT";"X4";"MMCX STRAIGHT, EDGE MOUNT JACK- 50 OHM";"Samtec Inc.";"MMCX-J-P-X-ST-EM1-MKT";"unknown";"unknown";"";"";"";
